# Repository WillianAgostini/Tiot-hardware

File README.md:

# Tiot-hardware

Diagrama do desenvolvimento.

## Organização do Projeto

- Tiot-firmware
    -  Desenvolvido com platformio
- shc
    -  Desenvolvido com Kicad
- mqtt-node
    - Desenvolvido como uma plataforma de teste, simulando o comportamento do hardware

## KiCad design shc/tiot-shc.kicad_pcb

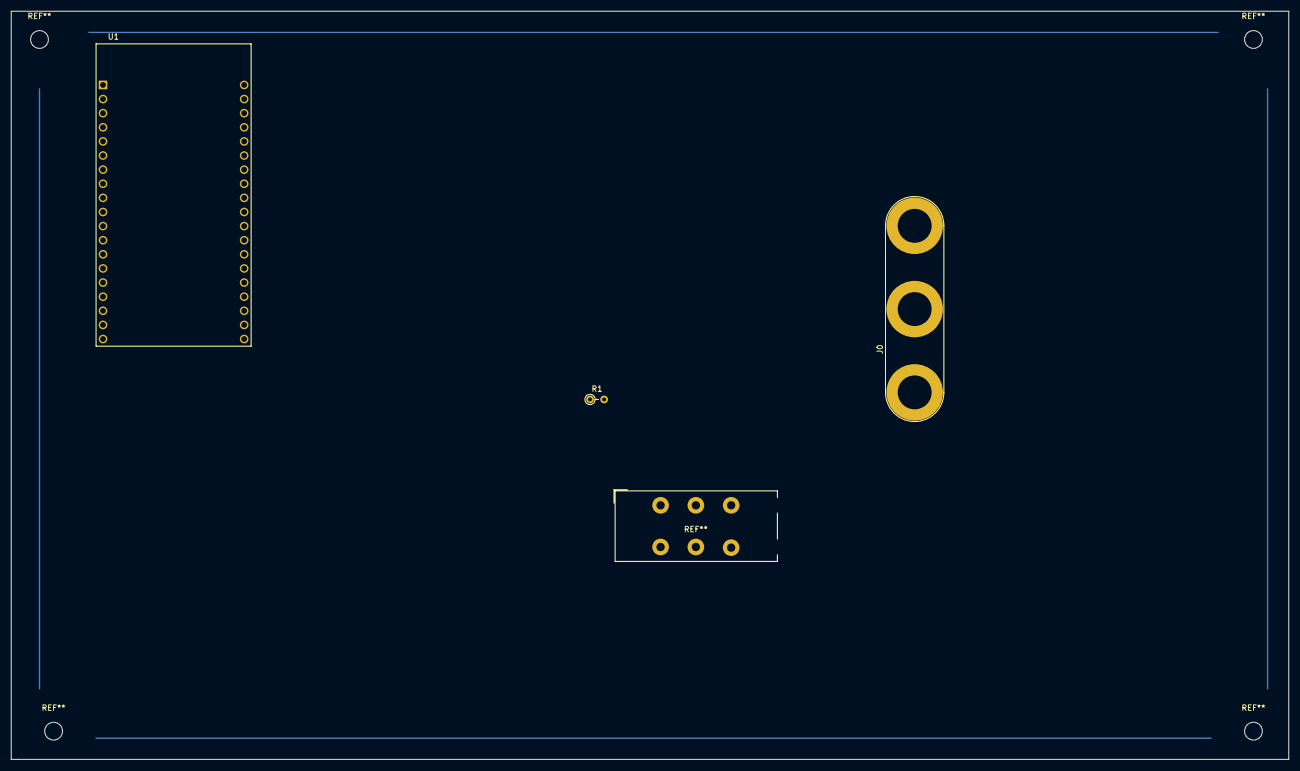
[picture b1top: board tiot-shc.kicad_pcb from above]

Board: 2 copper layers, 229.9 x 134.6 mm, 3 parts (0 on the bottom side), 3 nets.

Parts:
J0: Conn_01x03; Banana_Jack_3Pin
R1: R; R_Axial_DIN0204_L3.6mm_D1.6mm_P2.54mm_Vertical
U1: ESP32-DEVKITC-32D; MODULE_ESP32-DEVKITC-32D

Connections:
+3V3: J0.1, R1.1, U1.1
GND: J0.3, U1.20
unnamed: J0.2, R1.2, U1.32

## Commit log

2020-03-02 add mock do hardware
2020-03-09 renomeado pasta
2020-03-09 add over the air and Telnet server
2020-03-10 refatoração
2020-03-12 adicionado classse pra debug
2020-03-12 class debug
2020-03-14 add mqtt
2020-03-14 add lib sensor
2020-03-14 enviar temperatura por mqtt
2020-03-20 add eeprom
2020-03-23 get interval value of temperature
2020-03-23 criado classe para administrar termostato
2020-04-04 add projeto shc
2020-04-15 ajuste no intervalo da temperatura
2020-04-15 alterado intervalo
2020-04-15 resfriar até o mínimo
2020-04-16 add topicos para min e max
2020-04-28 atualizado comunicação com mqtt pois placa reiniciava
2020-04-30 funcionou!!
2020-05-19 publish status
2020-05-19 formatação ao enviar dados
2020-05-25 alterado forma de envio da temperatura e topico padrao
2020-06-04 wifi eduroam
2020-06-04 auth eduroam
2020-06-04 update ip
2020-06-28 gitignore
2020-06-28 add diagram
2020-06-28 removido arquivo lock
